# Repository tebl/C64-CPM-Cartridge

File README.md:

# C64 CP/M Cartridge

**UNTESTED**

Always wanted one of these for the original system, but they're hard to get so I've tried to recreate the cartridge itself for others to enjoy as well. For beginners and those with short memory, CP/M was professional choice of operating system for home computer markets - so if you wanted tax software, word processing and similar exciting tools this was the one you wanted for christmas. The system ran mainly on Z80-based systems while the Commodore 64 had a 6510 in it, so the cartridge was created in order to allow you to use the Z80 processor instead. Note that this is not a secondary processor, the Z80 shares all the main busses with the 6510 so only one of them can be active at a time.

There was no official schematic released for the module, none that I've seen anyway. Ruud Baltissen has taken upon himself the task of documenting the details of the module with a schematic, see his page at http://www.baltissen.org/newhtm/c64_cpm.htm for a lot more information on how the module works. My schematic has been transcribed from the one he made, then a PCB layout was done. Edge connector footprint was borrowed from the [Open16KCartridge](https://github.com/SukkoPera/OpenC64Cart16K) made by SukkoPera.

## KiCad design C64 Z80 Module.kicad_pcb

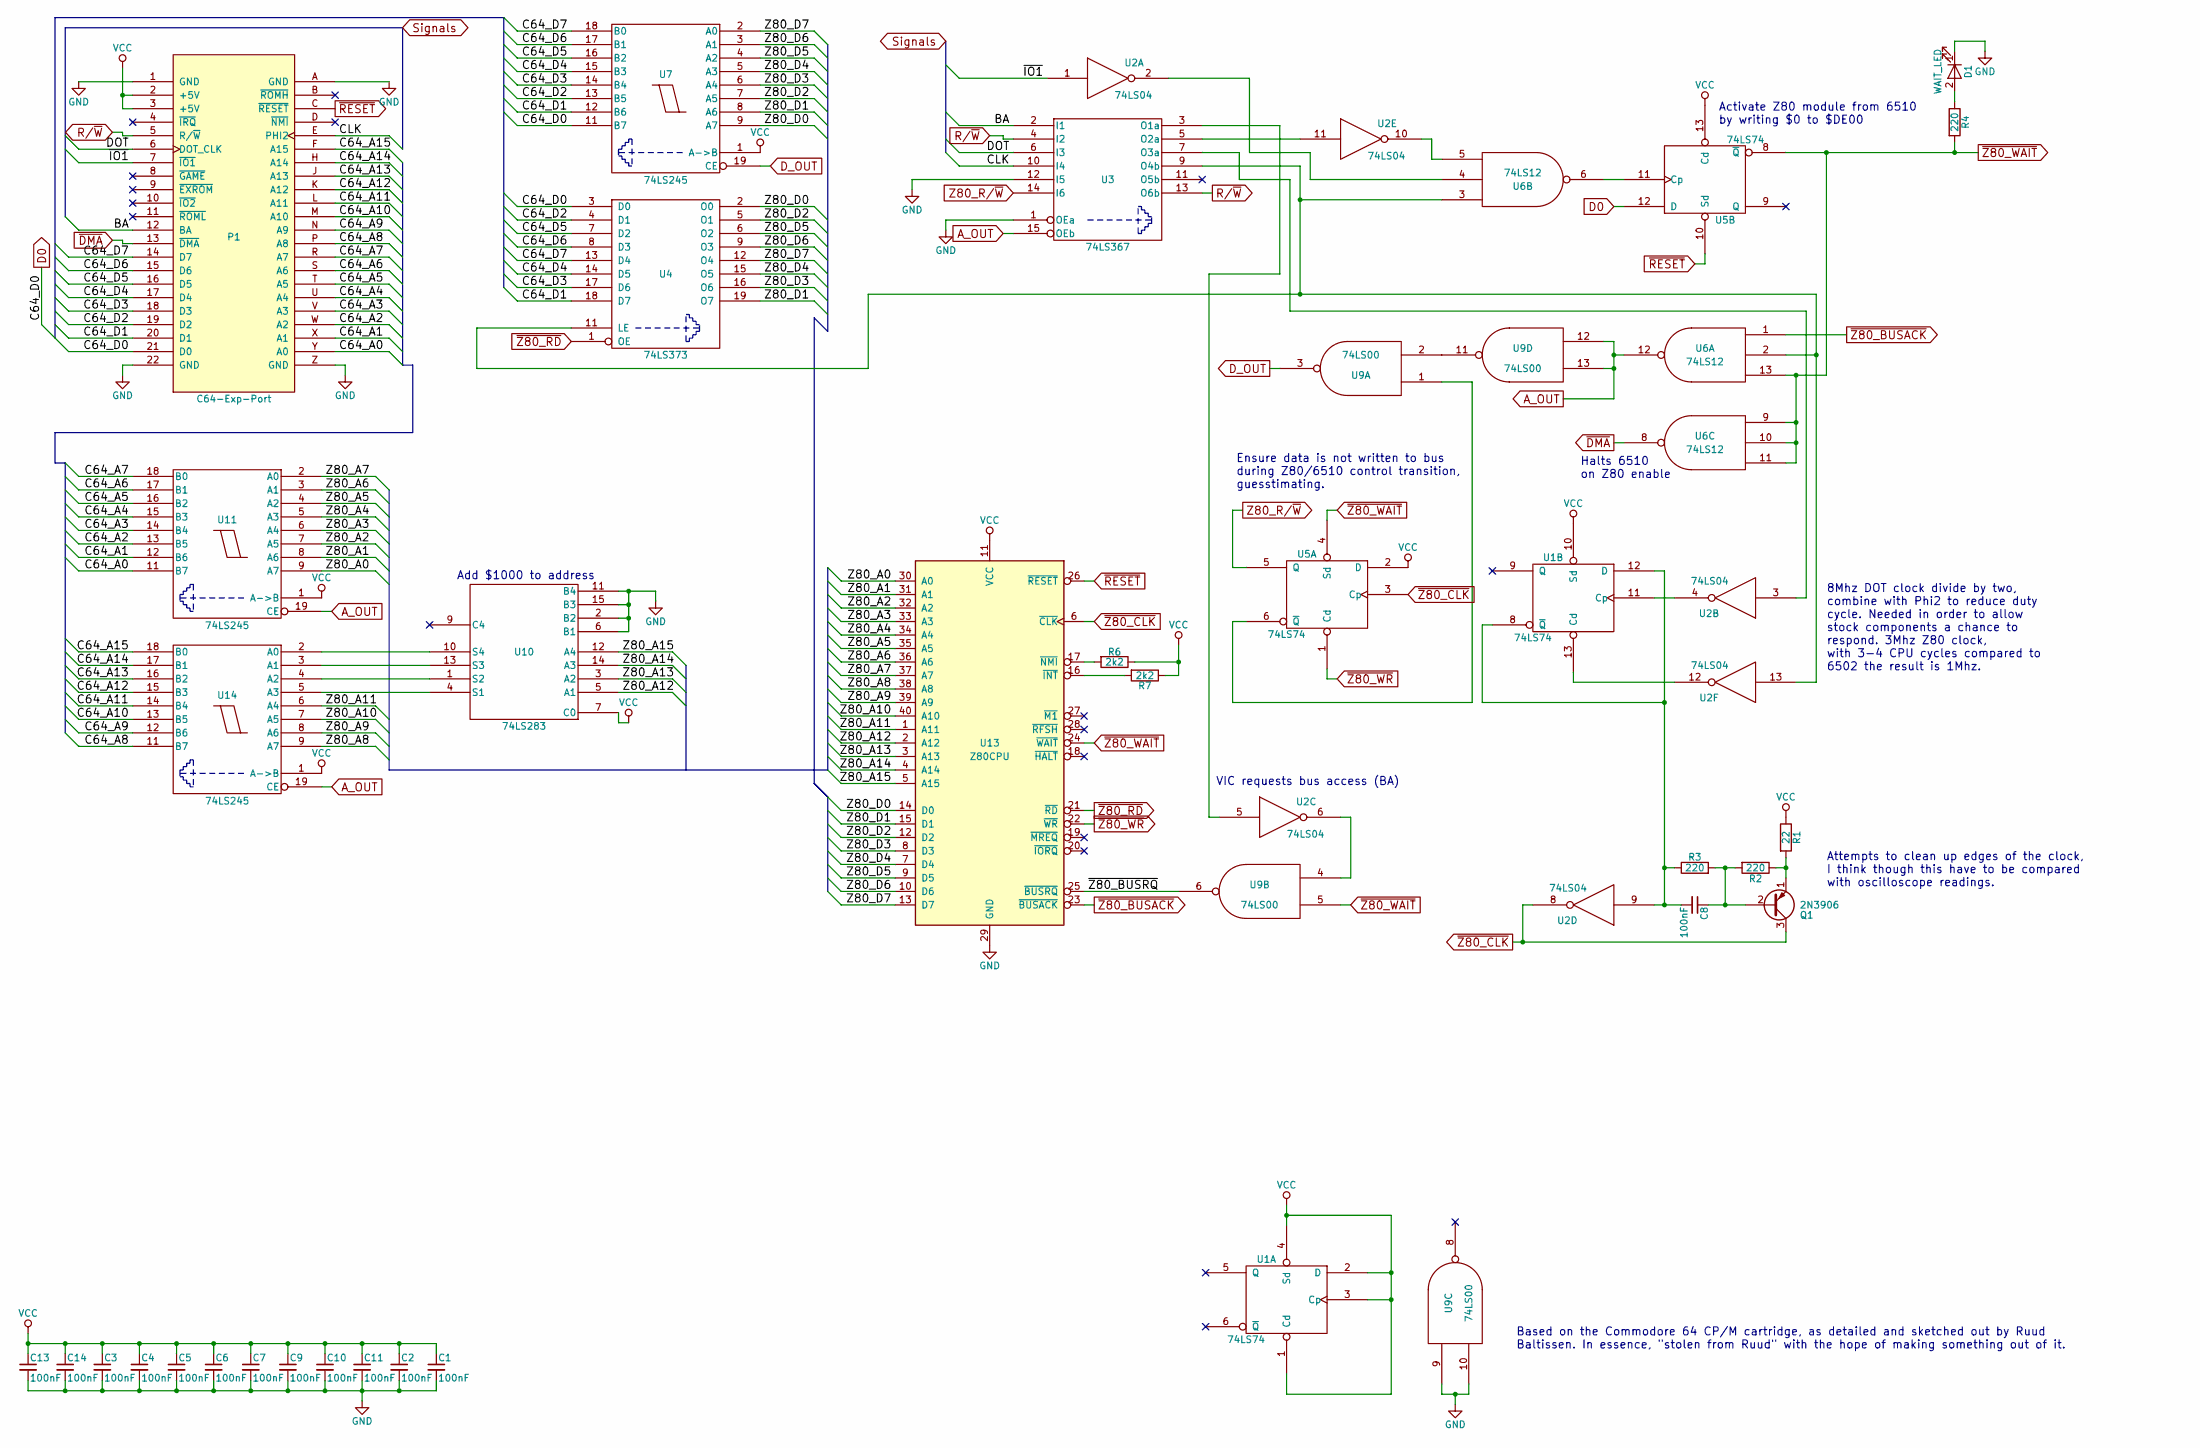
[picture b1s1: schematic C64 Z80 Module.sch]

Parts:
C1, C2, C3, C4, C5, C6, C7, C8, C9, C10, C11, C13, C14: 100nF; C_Disc_D4.7mm_W2.5mm_P5.00mm
D1: WAIT_LED; LED_D5.0mm
P1: C64-Exp-Port; C64-Cart
Q1: 2N3906; TO-92_Inline_Wide
R1: 22; R_Axial_DIN0207_L6.3mm_D2.5mm_P10.16mm_Horizontal
R2, R3, R4: 220; R_Axial_DIN0207_L6.3mm_D2.5mm_P10.16mm_Horizontal
R6, R7: 2k2; R_Axial_DIN0207_L6.3mm_D2.5mm_P10.16mm_Horizontal
U1, U5: 74LS74; DIP-14_W7.62mm_Socket
U2: 74LS04; DIP-14_W7.62mm_Socket
U3: 74LS367; DIP-16_W7.62mm_Socket
U4: 74LS373; DIP-20_W7.62mm_Socket
U6: 74LS12; DIP-14_W7.62mm_Socket
U7, U11, U14: 74LS245; DIP-20_W7.62mm_Socket
U9: 74LS00; DIP-14_W7.62mm_Socket
U10: 74LS283; DIP-16_W7.62mm_Socket
U13: Z80CPU; DIP-40_W15.24mm_Socket

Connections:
/BA: P1.12 (BA), U3.2 (I1)
/C64_A0: P1.Y (A0), U11.11 (B7)
/C64_A1: P1.X (A1), U11.12 (B6)
/C64_A2: P1.W (A2), U11.13 (B5)
/C64_A3: P1.V (A3), U11.14 (B4)
/C64_A4: P1.U (A4), U11.15 (B3)
/C64_A5: P1.T (A5), U11.16 (B2)
/C64_A6: P1.S (A6), U11.17 (B1)
/C64_A7: P1.R (A7), U11.18 (B0)
/C64_A8: P1.P (A8), U14.11 (B7)
/C64_A9: P1.N (A9), U14.12 (B6)
/C64_A10: P1.M (A10), U14.13 (B5)
/C64_A11: P1.L (A11), U14.14 (B4)
/C64_A12: P1.K (A12), U14.15 (B3)
/C64_A13: P1.J (A13), U14.16 (B2)
/C64_A14: P1.H (A14), U14.17 (B1)
/C64_A15: P1.F (A15), U14.18 (B0)
/C64_D1: P1.20 (D1), U4.18 (D7), U7.12 (B6)
/C64_D2: P1.19 (D2), U4.4 (D1), U7.13 (B5)
/C64_D3: P1.18 (D3), U4.17 (D6), U7.14 (B4)
/C64_D4: P1.17 (D4), U4.14 (D5), U7.15 (B3)
/C64_D5: P1.16 (D5), U4.7 (D2), U7.16 (B2)
/C64_D6: P1.15 (D6), U4.8 (D3), U7.17 (B1)
/C64_D7: P1.14 (D7), U4.13 (D4), U7.18 (B0)
/CLK: P1.E (PHI2), U3.10 (I4)
/DOT: P1.6 (DOT_CLK), U3.6 (I3)
/Z80_A0: U11.9 (A7), U13.30 (A0)
/Z80_A1: U11.8 (A6), U13.31 (A1)
/Z80_A2: U11.7 (A5), U13.32 (A2)
/Z80_A3: U11.6 (A4), U13.33 (A3)
/Z80_A4: U11.5 (A3), U13.34 (A4)
/Z80_A5: U11.4 (A2), U13.35 (A5)
/Z80_A6: U11.3 (A1), U13.36 (A6)
/Z80_A7: U11.2 (A0), U13.37 (A7)
/Z80_A8: U13.38 (A8), U14.9 (A7)
/Z80_A9: U13.39 (A9), U14.8 (A6)
/Z80_A10: U13.40 (A10), U14.7 (A5)
/Z80_A11: U13.1 (A11), U14.6 (A4)
/Z80_A12: U10.5 (A1), U13.2 (A12)
/Z80_A13: U10.3 (A2), U13.3 (A13)
/Z80_A14: U10.14 (A3), U13.4 (A14)
/Z80_A15: U10.12 (A4), U13.5 (A15)
/Z80_D0: U4.2 (O0), U7.9 (A7), U13.14 (D0)
/Z80_D1: U4.19 (O7), U7.8 (A6), U13.15 (D1)
/Z80_D2: U4.5 (O1), U7.7 (A5), U13.12 (D2)
/Z80_D3: U4.16 (O6), U7.6 (A4), U13.8 (D3)
/Z80_D4: U4.15 (O5), U7.5 (A3), U13.7 (D4)
/Z80_D5: U4.6 (O2), U7.4 (A2), U13.9 (D5)
/Z80_D6: U4.9 (O3), U7.3 (A1), U13.10 (D6)
/Z80_D7: U4.12 (O4), U7.2 (A0), U13.13 (D7)
/~IO1: P1.7 (~IO1), U2.1
/~Z80_BUSRQ: U9.6, U13.25 (~BUSRQ~)
A_OUT: U3.15 (OEb), U6.12, U9.12, U9.13, U11.19 (CE), U14.19 (CE)
D0: P1.21 (D0), U4.3 (D0), U5.12 (D), U7.11 (B7)
D_OUT: U7.19 (CE), U9.3
GND: C1.2, C2.2, C3.2, C4.2, C5.2, C6.2, C7.2, C9.2, C10.2, C11.2, C13.2, C14.2, D1.1 (K), P1.1 (GND), P1.22 (GND), P1.A (GND), P1.Z (GND), U1.7 (GND), U2.7 (GND), U3.1 (OEa), U3.8 (GND), U3.12 (I5), U4.10 (GND), U5.7 (GND), U6.7 (GND), U7.10 (GND), U9.7 (GND), U9.9, U9.10, U10.2 (B2), U10.6 (B1), U10.8 (GND), U10.11 (B4), U10.15 (B3), U11.10 (GND), U13.29 (GND), U14.10 (GND)
unnamed: C8.1, Q1.2 (B), R2.2, R3.2
unnamed: C8.2, R3.1, U1.8 (~Q), U1.12 (D), U2.9
unnamed: D1.2 (A), R4.1
unnamed: Q1.1 (E), R1.2, R2.1
unnamed: R6.2, U13.17 (~NMI~)
unnamed: R7.2, U13.16 (~INT~)
unnamed: U1.11 (Cp), U2.4
unnamed: U1.13 (Cd), U2.12
unnamed: U2.2, U6.4
unnamed: U2.3, U3.7 (O3a)
unnamed: U2.5, U3.3 (O1a)
unnamed: U2.6, U9.4
unnamed: U2.10, U6.5
unnamed: U2.11, U3.5 (O2a)
unnamed: U2.13, U3.9 (O4b), U4.11 (LE), U6.2, U6.3
unnamed: U5.6 (~Q), U9.1
unnamed: U5.11 (Cp), U6.6
unnamed: U9.2, U9.11
unnamed: U10.1 (S2), U14.4 (A2)
unnamed: U10.4 (S1), U14.5 (A3)
unnamed: U10.10 (S4), U14.2 (A0)
unnamed: U10.13 (S3), U14.3 (A1)
R/~W: P1.5 (R/~W), U3.4 (I2), U3.13 (O6b)
VCC: C1.1, C2.1, C3.1, C4.1, C5.1, C6.1, C7.1, C9.1, C10.1, C11.1, C13.1, C14.1, P1.2 (+5V), P1.3 (+5V), R1.1, R6.1, R7.1, U1.1 (Cd), U1.2 (D), U1.3 (Cp), U1.4 (Sd), U1.10 (Sd), U1.14 (VCC), U2.14 (VCC), U3.16 (VCC), U4.20 (VCC), U5.2 (D), U5.13 (Cd), U5.14 (VCC), U6.14 (VCC), U7.1 (A->B), U7.20 (VCC), U9.14 (VCC), U10.7 (C0), U10.16 (VCC), U11.1 (A->B), U11.20 (VCC), U13.11 (VCC), U14.1 (A->B), U14.20 (VCC)
Z80_R/~W: U3.14 (I6), U5.5 (Q)
~DMA: P1.13 (~DMA), U6.8
~RESET: P1.C (~RESET), U5.10 (Sd), U13.26 (~RESET~)
~Z80_BUSACK: U6.1, U13.23 (~BUSACK~)
~Z80_CLK: Q1.3 (C), U2.8, U5.3 (Cp), U13.6 (~CLK~)
~Z80_RD: U4.1 (OE), U13.21 (~RD~)
~Z80_WAIT: R4.2, U5.4 (Sd), U5.8 (~Q), U6.9, U6.10, U6.11, U6.13, U9.5, U13.24 (~WAIT~)
~Z80_WR: U5.1 (Cd), U13.22 (~WR~)

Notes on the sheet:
Add $1000 to address
Activate Z80 module from 6510 by writing $0 to $DE00
VIC requests bus access (BA)
Halts 6510 on Z80 enable
8Mhz DOT clock divide by two, combine with Phi2 to reduce duty cycle. Needed in order to allow stock components a chance to respond. 3Mhz Z80 clock, with 3-4 CPU cycles compared to 6502 the result is 1Mhz.
Based on the Commodore 64 CP/M cartridge, as detailed and sketched out by Ruud Baltissen. In essence, "stolen from Ruud" with the hope of making something out of it.
Attempts to clean up edges of the clock, I think though this have to be compared with oscilloscope readings.
Ensure data is not written to bus during Z80/6510 control transition, guesstimating.

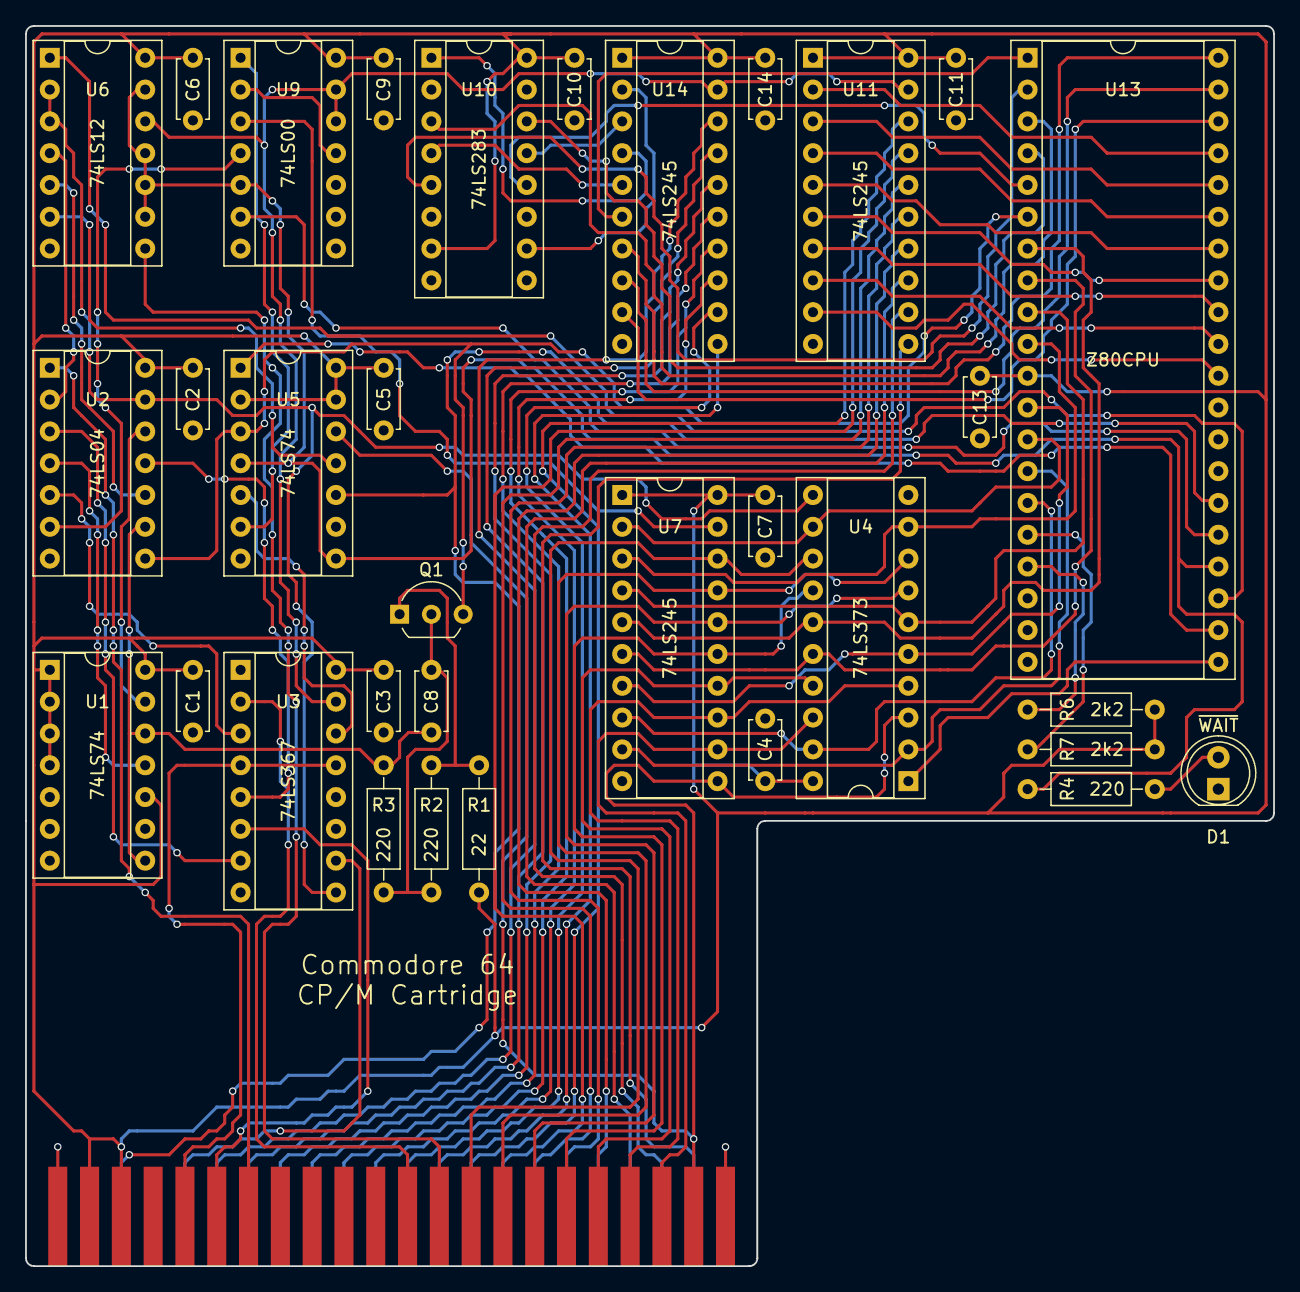
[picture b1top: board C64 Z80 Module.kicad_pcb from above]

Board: 2 copper layers, 99.7 x 99.1 mm, 34 parts (0 on the bottom side), 88 nets.

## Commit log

2019-07-01 Schematic transcribed
2019-07-01 Fixed errors (by ignoring them)
2019-07-01 Added notes to schematic for easier read
2019-07-02 Assigned footprints
2019-07-03 Layout done
2019-07-03 Gerber export
2019-07-03 Added README
